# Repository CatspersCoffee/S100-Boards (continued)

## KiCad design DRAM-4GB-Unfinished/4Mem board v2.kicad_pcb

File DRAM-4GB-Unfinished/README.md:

# 4GB DRAM Board (4Mem v2): unfinished

A Spartan-6 XC6SLX45 + DDR3 DIMM mezzanine for the [x86 32bit Memory Adapter Board](../x86-Memory-Adapter/). It plugs onto the adapter's P8/P9 headers and isn't an S-100 card itself (2015).

## Status
**Unfinished: schematic and placed, partly routed PCB only. It was never routed or built.**
- The `GERBERS/` folder in the original project is empty.
- None of the 124 DDR3 nets or the 74 P8/P9 signal nets has a track. The PCB file reports 478 unrouted connections.
- The board has no title or revision text.

## Hardware
| Ref | Part | Role |
|---|---|---|
| U1 | XC6SLX45-2FGG484C | FPGA, DDR3 interface to the adapter board |
| U2 | 240-pin DDR3 DIMM socket | 64-bit unbuffered DIMM, 2 ranks |
| U3 | XCF08P (TSOP48) | FPGA configuration flash |
| U12 | PIC18F2520 (QFN28) | on the DIMM SPD I2C bus, 6 lines to the FPGA |
| U9 | oscillator | FPGA clock into ball M3 (GCLK); a 62.5 MHz 2.5 V part in `digikey.xlsx` |
| U5 | AZ1084 | 3.3 V from +8 V |
| U6 | NCP565 | 1.2 V (FPGA core) |
| U7 | LT1764EQ-1.5 | 1.5 V DIMM supply |
| U8 | RT9026 | DDR3 VTT / VREF |
| U4, U10 | LM1117-1.8, LM1117-2.5 | XCF08P core, oscillator |
| P8, P9 | 2x20 headers | to the x86 32bit Memory Adapter Board |
| P11 | 2x2 header | JTAG (TDI, TDO, TMS, TCK) |
| P5 | 2x6 header | PIC programming (MCLR/PGD/PGC) and UART (TX/RX) |
| SW1 | push button | FPGA PROG_B |
| D1, D2 | LEDs | POWER, FPGA DONE (via Q1) |

- Board: 150.4 x 75.2 mm, rounded corners, four corner mounting holes, 6 copper layers (Top, GND, Sig1, Sig2, POWER, Bottom).
- KiCad (2013-07-07 BZR 4022)-stable.

## How it works (as drawn)
- **P8/P9:** these carry 72 FPGA I/O lines plus +8 V (P8 pins 1–4) and GND (P9 pins 39–40). The pins and positions match P8/P9 on the [x86 32bit Memory Adapter Board](../x86-Memory-Adapter/): its 32-bit data bus (bD0–31), address bA2–22 and CPLD lines.
- **DDR3:** the FPGA connects to the whole DIMM interface: A0–A15, BA0–2, DQ0–63, DQS0–7, DM0–7, CK0/CK1, CKE0/1, S0/S1, ODT0/1, RAS/CAS/WE.
- **Configuration:** the FPGA boots from the XCF08P (D0–D7, CCLK), which shares the JTAG chain with the FPGA. SW1 pulls PROGRAM_B.
- **DIMM reset:** FPGA DONE drives the DIMM RESET# pin (through R8, 0 Ω) and the DONE LED.
- **PIC18F2520:** reads the DIMM SPD EEPROM (SCL/SDA, 10K pull-ups) and has 6 lines to the FPGA.
- **Power:** the board makes all its rails from the +8 V on P8.

## Files
| File | What it is |
|---|---|
| `4Mem board v2.sch` | schematic (single sheet) |
| `4Mem board v2-cache.lib` | symbol cache |
| `4Mem board v2.kicad_pcb` | PCB (placed, partly routed) |
| `4Mem board v2.pro` | KiCad project |
| `4Mem board v2.net`, `.cmp` | netlist and footprint assignments |
| `digikey.xlsx` | DigiKey parts list (NZD), including parts for the sibling SRAM/adapter boards |

There is no FPGA project for this board.

## History
- The git history replays the original dated backups, from 2015-05-03 to 2015-06-21.
- The project started as a copy of the [4Mbit (128K x 32) SRAM module](../x86-Memory-Adapter/sram-module/). It has the same outline and P8/P9 positions, and the module's "4Mbit (128K x 32)" text is still in the PCB file, outside the board edge.
- The last file activity is an autorouter (Specctra `.dsn`) export of the same PCB on 2016-12-06. It isn't included.

## Things to check (TODO)
- **FPGA supplies:** nets `/V1.2temp`, `/V1.5temp` and `/V3.3temp` are not joined to the regulator outputs `/V1.2`, `/V1.5` and `/V3.3`.
- **U4/U10 input:** `/+8Vitemp`, the input to U4 and U10, is not joined to `/+8Vi`.
- **XCF08P supply:** the XCF08P I/O supply is on a separate net, `/V3.3temp2`.
- **Loose pins:** one side of LEDs D5 and D6, and the PIC PGM pin, are unconnected.
- **DDR3 balls vs memory controller:** the DDR3 balls don't follow the Spartan-6 hard memory controller (MCB) pinout. For example, A0 is on G19, an M1A10 ball. The 64-bit DIMM is also wider than one MCB.
- **Net name:** `/DDR3_OFT1` is the DIMM ODT1 signal.
- **JTAG header:** P11 has no GND or VREF pin.
- **Schematic title block:** it still says "noname.sch".
- **Copper planes:** no copper zones are poured on the GND or POWER layers.

## Credits
- The DDR3 pin assignment follows a Spartan-6 DDR3 UDIMM reference document.
- The FPGA symbol comes from the author's own KiCad library.

## License
Hardware: CERN-OHL-S-2.0 for the original work in this folder; see the repo NOTICE for third-party parts.

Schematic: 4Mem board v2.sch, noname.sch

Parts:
C1, C4, C6, C14, C22, C23, C25, C26, C28, C29, C30, C31, C32, C33, C35, C37, C39, C40, C41, C42, C43, C45: 0.1 uF; C2
C2, C27: 0.1 uF
C3, C5, C7, C8, C9, C10, C11, C12, C13, C15, C16, C17, C18, C19, C20, C21, C24, C34, C36, C38, C44, C46, C47, C48: 10 uF
D1: POWER
D2: LED
D5, D6: LED; LEDV
P1, P2, P3, P4: CONN_1
P5: CONN_6X2
P8, P9: CONN_20X2; 8MB_SRAM
P11: CONN_2X2
Q1: ^^NPN-BC817-SOT323
R1, R2, R5, R6, R11: 330
R3, R4, R7, R9, R10: 4K7
R8: 0
R12, R13: 10K
SW1: PROG_B
U1: XC6SLX45-2FGG484C
U2: DDR3_DIMM_240PIN
U3: XCF08P-VO48/TSOP48
U4: LM1117MP-1.8
U5: AZ1084
U6: NCP565
U7: LT1764EQ-1.5
U8: RT9026_MSOP-10
U9: FPGA_CLK_0; Digikey CTX285LVCT-ND
U10: LM1117MP-2.5
U12: PIC18F2520-28QFN

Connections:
/+8Vi: C5.1, C7.1, C9.1, C10.1, C18.1, C34.1, P8.1, P8.2, P8.3, P8.4, U5.3 (VI), U6.1 (VI), U7.1 (~SHDN), U7.2 (VI)
/+8Vitemp: C3.1, C8.1, C44.1, U4.3 (VI), U10.3 (VI)
/DDR3_A0: U1.G19 (IO_L33P_A15_M1A10_1), U2.188 (A0)
/DDR3_A1: U1.A21 (IO_L20N_1), U2.181 (A1)
/DDR3_A2: U1.A20 (IO_L20P_1), U2.61 (A2)
/DDR3_A3: U1.A2 (IO_L83P_3), U2.180 (A3)
/DDR3_A4: U1.H8 (IO_L59N_3), U2.59 (A4)
/DDR3_A5: U1.G6 (IO_L55P_M3A13_3), U2.58 (A5)
/DDR3_A6: U1.F5 (IO_L55N_M3A14_3), U2.178 (A6)
/DDR3_A7: U1.G4 (IO_L51P_M3A10_3), U2.56 (A7)
/DDR3_A8: U1.H6 (IO_L49P_M3A7_3), U2.177 (A8)
/DDR3_A9: U1.J7 (IO_L59P_3), U2.175 (A9)
/DDR3_A10: U1.H19 (IO_L34P_A13_M1WE_1), U2.70 (A10/AP)
/DDR3_A11: U1.H5 (IO_L49N_M3A2_3), U2.55 (A11)
/DDR3_A12: U1.J6 (IO_L45N_M3ODT_3), U2.174 (A12/BC)
/DDR3_A13: U1.M20 (IO_L42P_GCLK7_M1UDM_1), U2.196 (A13)
/DDR3_A14: U1.K4 (IO_L43N_GCLK22_IRDY2_M3CASN_3), U2.172 (A14)
/DDR3_A15: U1.K3 (IO_L44P_GCLK21_M3A5_3), U2.171 (A15)
/DDR3_BA0: U1.J17 (IO_L36P_A9_M1BA0_1), U2.71 (BA0)
/DDR3_BA1: U1.H18 (IO_L34N_A12_M1BA2_1), U2.190 (BA1)
/DDR3_BA2: U1.J4 (IO_L44N_GCLK20_M3A6_3), U2.52 (BA2)
/DDR3_CAS: U1.K18 (IO_L61N_1), U2.74 (~CAS)
/DDR3_CK0h: U1.F18 (IO_L30P_A21_M1RESET_1), U2.184 (CK0)
/DDR3_CK0l: U1.F19 (IO_L30N_A20_M1A11_1), U2.185 (~CK0)
/DDR3_CK1h: U1.B21 (IO_L19P_1), U2.63 (CK1)
/DDR3_CK1l: U1.B22 (IO_L19N_1), U2.64 (~CK1)
/DDR3_CKE0: U1.K5 (IO_L43P_GCLK23_M3RASN_3), U2.50 (CKE0)
/DDR3_CKE1: U1.K6 (IO_L45P_M3A3_3), U2.169 (CKE1)
/DDR3_DM0: U1.V1 (IO_L32N_M3DQ15_3), U2.125 (DM0)
/DDR3_DM1: U1.P1 (IO_L36N_M3DQ9_3), U2.134 (DM1)
/DDR3_DM2: U1.J1 (IO_L41N_GCLK26_M3DQ5_3), U2.143 (DM2)
/DDR3_DM3: U1.E3 (IO_L52P_M3A8_3), U2.152 (DM3)
/DDR3_DM4: U1.D22 (IO_L31N_A18_M1A12_1), U2.203 (DM4)
/DDR3_DM5: U1.H22 (IO_L41N_GCLK8_M1CASN_1), U2.212 (DM5)
/DDR3_DM6: U1.M19 (IO_L53P_1), U2.221 (DM6)
/DDR3_DM7: U1.U22 (IO_L51N_M1DQ13_1), U2.230 (DM7)
/DDR3_DQ0: U1.W3 (IO_L2P_3), U2.3 (DQ0)
/DDR3_DQ1: U1.W1 (IO_L2N_3), U2.4 (DQ1)
/DDR3_DQ2: U1.U3 (IO_L33P_M3DQ12_3), U2.9 (DQ2)
/DDR3_DQ3: U1.T1 (IO_L34N_M3UDQSN_3), U2.10 (DQ3)
/DDR3_DQ4: U1.Y2 (IO_L1P_3), U2.122 (DQ4)
/DDR3_DQ5: U1.V2 (IO_L32P_M3DQ14_3), U2.123 (DQ5)
/DDR3_DQ6: U1.U1 (IO_L33N_M3DQ13_3), U2.128 (DQ6)
/DDR3_DQ7: U1.T2 (IO_L34P_M3UDQS_3), U2.129 (DQ7)
/DDR3_DQ8: U1.T4 (IO_L9P_3), U2.12 (DQ8)
/DDR3_DQ9: U1.R3 (IO_L35P_M3DQ10_3), U2.13 (DQ9)
/DDR3_DQ10: U1.M1 (IO_L38N_M3DQ3_3), U2.18 (DQ10)
/DDR3_DQ11: U1.L1 (IO_L39N_M3LDQSN_3), U2.19 (DQ11)
/DDR3_DQ12: U1.T3 (IO_L9N_3), U2.131 (DQ12)
/DDR3_DQ13: U1.R1 (IO_L35N_M3DQ11_3), U2.132 (DQ13)
/DDR3_DQ14: U1.M2 (IO_L38P_M3DQ2_3), U2.137 (DQ14)
/DDR3_DQ15: U1.L3 (IO_L39P_M3LDQS_3), U2.138 (DQ15)
/DDR3_DQ16: U1.K1 (IO_L40N_M3DQ7_3), U2.21 (DQ16)
/DDR3_DQ17: U1.K2 (IO_L40P_M3DQ6_3), U2.22 (DQ17)
/DDR3_DQ18: U1.H2 (IO_L47P_M3A0_3), U2.27 (DQ18)
/DDR3_DQ19: U1.G1 (IO_L48N_M3BA1_3), U2.28 (DQ19)
/DDR3_DQ20: U1.M5 (IO_L31P_3), U2.140 (DQ20)
/DDR3_DQ21: U1.J3 (IO_L41P_GCLK27_M3DQ4_3), U2.141 (DQ21)
/DDR3_DQ22: U1.H1 (IO_L47N_M3A1_3), U2.146 (DQ22)
/DDR3_DQ23: U1.G3 (IO_L48P_M3BA0_3), U2.147 (DQ23)
/DDR3_DQ24: U1.F1 (IO_L50N_M3BA2_3), U2.30 (DQ24)
/DDR3_DQ25: U1.E1 (IO_L52N_M3A9_3), U2.31 (DQ25)
/DDR3_DQ26: U1.C3 (IO_L54P_M3RESET_3), U2.36 (DQ26)
/DDR3_DQ27: U1.B2 (IO_L60P_3), U2.37 (DQ27)
/DDR3_DQ28: U1.F3 (IO_L51N_M3A4_3), U2.149 (DQ28)
/DDR3_DQ29: U1.F2 (IO_L50P_M3WE_3), U2.150 (DQ29)
/DDR3_DQ30: U1.C1 (IO_L54N_M3A11_3), U2.155 (DQ30)
/DDR3_DQ31: U1.B1 (IO_L60N_3), U2.156 (DQ31)
/DDR3_DQ32: U1.C22 (IO_L32N_A16_M1A9_1), U2.81 (DQ32)
/DDR3_DQ33: U1.C20 (IO_L32P_A17_M1A8_1), U2.82 (DQ33)
/DDR3_DQ34: U1.E20 (IO_L35P_A11_M1A7_1), U2.87 (DQ34)
/DDR3_DQ35: U1.F22 (IO_L37N_A6_M1A1_1), U2.88 (DQ35)
/DDR3_DQ36: U1.C19 (IO_L1P_A25_1), U2.200 (DQ36)
/DDR3_DQ37: U1.D21 (IO_L31P_A19_M1CKE_1), U2.201 (DQ37)
/DDR3_DQ38: U1.E22 (IO_L35N_A10_M1A2_1), U2.206 (DQ38)
/DDR3_DQ39: U1.F21 (IO_L37P_A7_M1A0_1), U2.207 (DQ39)
/DDR3_DQ40: U1.G22 (IO_L39N_M1ODT_1), U2.90 (DQ40)
/DDR3_DQ41: U1.H21 (IO_L41P_GCLK9_IRDY1_M1RASN_1), U2.91 (DQ41)
/DDR3_DQ42: U1.J20 (IO_L43P_GCLK5_M1DQ4_1), U2.96 (DQ42)
/DDR3_DQ43: U1.K21 (IO_L44P_A3_M1DQ6_1), U2.97 (DQ43)
/DDR3_DQ44: U1.F20 (IO_L33N_A14_M1A4_1), U2.209 (DQ44)
/DDR3_DQ45: U1.G20 (IO_L39P_M1A3_1), U2.210 (DQ45)
/DDR3_DQ46: U1.J22 (IO_L43N_GCLK4_M1DQ5_1), U2.215 (DQ46)
/DDR3_DQ47: U1.K22 (IO_L44N_A2_M1DQ7_1), U2.216 (DQ47)
/DDR3_DQ48: U1.L20 (IO_L45P_A1_M1LDQS_1), U2.99 (DQ48)
/DDR3_DQ49: U1.M21 (IO_L46P_FCS_B_M1DQ2_1), U2.100 (DQ49)
/DDR3_DQ50: U1.P21 (IO_L48P_HDC_M1DQ8_1), U2.105 (DQ50)
/DDR3_DQ51: U1.R22 (IO_L49N_M1DQ11_1), U2.106 (DQ51)
/DDR3_DQ52: U1.L22 (IO_L45N_A0_M1LDQSN_1), U2.218 (DQ52)
/DDR3_DQ53: U1.M22 (IO_L46N_FOE_B_M1DQ3_1), U2.219 (DQ53)
/DDR3_DQ54: U1.P22 (IO_L48N_M1DQ9_1), U2.224 (DQ54)
/DDR3_DQ55: U1.R20 (IO_L49P_M1DQ10_1), U2.225 (DQ55)
/DDR3_DQ56: U1.T22 (IO_L50N_M1UDQSN_1), U2.108 (DQ56)
/DDR3_DQ57: U1.U20 (IO_L51P_M1DQ12_1), U2.109 (DQ57)
/DDR3_DQ58: U1.V21 (IO_L52P_M1DQ14_1), U2.114 (DQ58)
/DDR3_DQ59: U1.W22 (IO_L60N_1), U2.115 (DQ59)
/DDR3_DQ60: U1.P19 (IO_L59P_1), U2.227 (DQ60)
/DDR3_DQ61: U1.T21 (IO_L50P_M1UDQS_1), U2.228 (DQ61)
/DDR3_DQ62: U1.V22 (IO_L52N_M1DQ15_1), U2.233 (DQ62)
/DDR3_DQ63: U1.W20 (IO_L60P_1), U2.234 (DQ63)
/DDR3_DQS0h: U1.U4 (IO_L10P_3), U2.7 (DQS0)
/DDR3_DQS0l: U1.V3 (IO_L10N_3), U2.6 (~DQS0)
/DDR3_DQS1h: U1.N1 (IO_L37N_M3DQ1_3), U2.16 (DQS1)
/DDR3_DQS1l: U1.N3 (IO_L37P_M3DQ0_3), U2.15 (~DSQ1)
/DDR3_DQS2h: U1.H3 (IO_L46N_M3CLKN_3), U2.25 (DQS2)
/DDR3_DQS2l: U1.H4 (IO_L46P_M3CLK_3), U2.24 (~DQS2)
/DDR3_DQS3h: U1.D2 (IO_L53P_M3CKE_3), U2.34 (DQS3)
/DDR3_DQS3l: U1.D1 (IO_L53N_M3A12_3), U2.33 (~DQS3)
/DDR3_DQS4h: U1.D19 (IO_L29P_A23_M1A13_1), U2.85 (DQS4)
/DDR3_DQS4l: U1.D20 (IO_L29N_A22_M1A14_1), U2.84 (~DQS4)
/DDR3_DQS5h: U1.J19 (IO_L38N_A4_M1CLKN_1), U2.94 (DQS5)
/DDR3_DQS5l: U1.H20 (IO_L38P_A5_M1CLK_1), U2.93 (~DQS5)
/DDR3_DQS6h: U1.N20 (IO_L47P_FWE_B_M1DQ0_1), U2.103 (DQS6)
/DDR3_DQS6l: U1.N22 (IO_L47N_LDC_M1DQ1_1), U2.102 (~DQS6)
/DDR3_DQS7h: U1.T19 (IO_L74P_AWAKE_1), U2.112 (DQS7)
/DDR3_DQS7l: U1.T20 (IO_L74N_DOUT_BUSY_1), U2.111 (~DQS7)
/DDR3_ODT0: U1.L19 (IO_L42N_GCLK6_TRDY1_M1LDM_1), U2.195 (~DQS0)
/DDR3_OFT1: U1.P20 (IO_L59N_1), U2.77 (OFT1)
/DDR3_RAS: U1.K17 (IO_L36N_A8_M1BA1_1), U2.192 (~RAS)
/DDR3_S0l: U1.K19 (IO_L40N_GCLK10_M1A6_1), U2.193 (~SO)
/DDR3_S1l: U1.L17 (IO_L61P_1), U2.76 (~S1)
/DDR3_SCL: R12.1, U2.118 (SCL), U12.11 (SCK/SCL/RC3)
/DDR3_SDA: R13.1, U2.238 (SDA), U12.12 (SDI/SDA/RC4)
/DDR3_VREF: C23.1, C26.1, C29.1, C31.1, U2.1 (VREF), U2.67 (VREF), U8.6 (VTTREF)
/DDR3_VTT: C22.1, C25.1, C28.1, C30.1, U2.120 (VTT), U2.240 (VTT), U8.3 (VTT), U8.5 (VTTSNS)
/DDR3_WE: U1.K20 (IO_L40P_GCLK11_M1A5_1), U2.73 (~WE)
/DONE_LED_SIGNAL: Q1.1 (B), R8.1, U2.168 (~RESET)
/FPGA_CCLK_2: R3.2, R4.1, U1.Y21 (IO_L1P_CCLK_2), U3.12 (CLK)
/FPGA_CLK_0: U1.M3 (IO_L42P_GCLK25_TRDY2_M3UDM_3), U9.3 (OUT)
/FPGA_DONE: R8.2, R11.2, U1.Y22 (DONE_2), U3.13 (CE)
/FPGA_INIT_B: R7.2, U1.T6 (IO_L65P_INIT_B_2), U3.11 (OE/RST)
/FPGA_PROGRAM_B: R10.2, SW1.2, U1.AA1 (PROGRAM_B_2)
/FPGA_TDI: P11.3, U1.E18 (TDI)
/FPGA_TDO: U1.A19 (TDO), U3.19 (TDI)
/IO_000: P8.13, U1.B14 (IO_L50P_0)
/IO_001: P8.15, U1.A14 (IO_L50N_0)
/IO_002: P8.17, U1.A17 (IO_L64N_SCP4_0)
/IO_003: P8.19, U1.B18 (IO_L65P_SCP3_0)
/IO_004: P8.21, U1.A16 (IO_L63N_SCP6_0)
/IO_005: P8.23, U1.C17 (IO_L64P_SCP5_0)
/IO_006: P8.25, U1.C16 (IO_L62N_VREF_0)
/IO_007: P8.27, U1.B16 (IO_L63P_SCP7_0)
/IO_008: P8.29, U1.B6 (IO_L4P_0)
/IO_009: P8.31, U1.A6 (IO_L4N_0)
/IO_010: P8.33, U1.C7 (IO_L5P_0)
/IO_011: P8.35, U1.A7 (IO_L5N_0)
/IO_012: P8.37, U1.B8 (IO_L6P_0)
/IO_013: P8.39, U1.A8 (IO_L6N_0)
/IO_014: P9.1, U1.B10 (IO_L34P_GCLK19_0)
/IO_015: P9.3, U1.A10 (IO_L34N_GCLK18_0)
/IO_016: P9.5, U1.AB9 (IO_L43N_2)
/IO_017: P9.7, U1.Y9 (IO_L43P_2)
/IO_018: P9.9, U1.Y10 (IO_L44N_2)
/IO_019: P9.11, U1.W10 (IO_L44P_2)
/IO_020: P9.13, U1.Y16 (IO_L17P_2)
/IO_021: P9.15, U1.W15 (IO_L17N_2)
/IO_022: P9.17, U1.B12 (IO_L37P_GCLK13_0)
/IO_023: P9.19, U1.A12 (IO_L37N_GCLK12_0)
/IO_024: P9.21, U1.C13 (IO_L38P_0)
/IO_025: P9.23, U1.A13 (IO_L38N_VREF_0)
/IO_026: P9.25, U1.D14 (IO_L49P_0)
/IO_027: P9.27, U1.C14 (IO_L49N_0)
/IO_028: P9.29, U1.U16 (IO_L8N_2)
/IO_029: P9.31, U1.U17 (IO_L8P_2)
/IO_030: P9.33, U1.W8 (IO_L46P_2)
/IO_031: P9.35, U1.Y8 (IO_L47N_2)
/IO_032: P9.37, U1.C6 (IO_L3N_0)
/IO_033: P9.34, U1.D6 (IO_L3P_0)
/IO_034: P9.36, U1.A5 (IO_L2N_0)
/IO_035: P9.38, U1.C5 (IO_L2P_0)
/IO_072: P8.5, U1.AA18 (IO_L14P_D11_2)
/IO_073: P8.7, U1.AB18 (IO_L14N_D12_2)
/IO_074: P8.9, U1.U10 (IO_L52N_2)
/IO_075: P8.11, U1.T10 (IO_L52P_2)
/IO_076: P9.18, U1.W14 (IO_L20P_2)
/IO_077: P9.20, U1.Y14 (IO_L20N_2)
/IO_078: P9.22, U1.Y15 (IO_L21P_2)
/IO_079: P9.24, U1.AB15 (IO_L21N_2)
/IO_080: P9.26, U1.AB12 (IO_L31N_GCLK30_D15_2)
/IO_081: P9.28, U1.AA12 (IO_L31P_GCLK31_D14_2)
/IO_082: P9.30, U1.AB11 (IO_L32N_GCLK28_2)
/IO_083: P9.32, U1.Y11 (IO_L32P_GCLK29_2)
/IO_084: P9.6, U1.AB5 (IO_L54N_2)
/IO_085: P9.8, U1.Y5 (IO_L54P_2)
/IO_086: P9.10, U1.AB3 (IO_L58N_2)
/IO_087: P9.12, U1.Y3 (IO_L58P_2)
/IO_088: P9.14, U1.Y6 (IO_L53N_2)
/IO_089: P9.16, U1.W6 (IO_L53P_2)
/IO_090: P8.38, U1.AB10 (IO_L41N_VREF_2)
/IO_091: P8.40, U1.AA10 (IO_L41P_2)
/IO_092: P9.2, U1.AB4 (IO_L57N_2)
/IO_093: P9.4, U1.AA4 (IO_L57P_2)
/IO_094: P8.6, U1.W12 (IO_L29P_GCLK3_2)
/IO_095: P8.8, U1.Y12 (IO_L29N_GCLK2_2)
/IO_096: P8.10, U1.AA16 (IO_L19P_2)
/IO_097: P8.12, U1.AB16 (IO_L19N_2)
/IO_098: P8.14, U1.AA14 (IO_L16P_2)
/IO_099: P8.16, U1.AB14 (IO_L16N_VREF_2)
/IO_100: P8.18, U1.Y19 (IO_L5P_2)
/IO_101: P8.20, U1.AB19 (IO_L5N_2)
/IO_102: P8.22, U1.Y17 (IO_L15P_2)
/IO_103: P8.24, U1.AB17 (IO_L15N_2)
/IO_104: P8.26, U1.W18 (IO_L6P_2)
/IO_105: P8.28, U1.Y18 (IO_L6N_2)
/IO_106: P8.30, U1.U6 (IO_L63P_2)
/IO_107: P8.32, U1.V5 (IO_L63N_2)
/IO_108: P8.34, U1.AB8 (IO_L45N_2)
/IO_109: P8.36, U1.AA8 (IO_L45P_2)
/PF_D0: U1.AA20 (IO_L3P_D0_DIN_MISO_MISO1_2), U3.28 (D0)
/PF_D1: U1.U14 (IO_L12P_D1_MISO2_2), U3.29 (D1)
/PF_D2: U1.U13 (IO_L12N_D2_MISO3_2), U3.32 (D2)
/PF_D3: U1.AA6 (IO_L49P_D3_2), U3.33 (D3)
/PF_D4: U1.AB6 (IO_L49N_D4_2), U3.43 (D4)
/PF_D5: U1.W4 (IO_L62P_D5_2), U3.44 (D5)
/PF_D6: U1.Y4 (IO_L62N_D6_2), U3.47 (D6)
/PF_D7: U1.Y7 (IO_L48P_D7_2), U3.48 (D7)
/PF_TDO: P11.1, U3.22 (TDO)
/PIC_IO1: U1.W11 (IO_L42N_2), U12.18 (INT0/FLT0/AN12/RB0)
/PIC_IO2: U1.V11 (IO_L42P_2), U12.19 (INT1/AN10/RB1)
/PIC_IO3: U1.V19 (IO_L9P_2), U12.20 (INT2/AN8/RB2)
/PIC_IO4: U1.V18 (IO_L9N_2), U12.21 (CCP2/AN9/RB3)
/PIC_IO5: U1.R16 (IO_L10P_2), U12.8 (T1OSO/T13CKI/RC0)
/PIC_IO6: U1.R15 (IO_L10N_2), U12.9 (CCP2/T1OSI/CCP2/RC1)
/PIC_MCLR: P5.1, U12.26 (_MCLR/VPP/RE3)
/PIC_PGC: P5.9, U12.24 (KBI2/PGC/RB6)
/PIC_PGD: P5.7, U12.25 (KBI3/PGD/RB7)
/PIC_RX: P5.4, P5.10, U12.15 (RX/DT/RC7)
/V1.2: C12.1, C16.1, C20.1, U6.3 (VO)
/V1.2temp: C2.1, C33.1, C37.1, C40.1, C41.1, C43.1, U1.J8 (VCCINT), U1.J10 (VCCINT), U1.J12 (VCCINT), U1.J14 (VCCINT), U1.K9 (VCCINT), U1.K11 (VCCINT), U1.K13 (VCCINT), U1.L10 (VCCINT), U1.L12 (VCCINT), U1.L14 (VCCINT), U1.M9 (VCCINT), U1.M11 (VCCINT), U1.M13 (VCCINT), U1.N10 (VCCINT), U1.N12 (VCCINT), U1.N14 (VCCINT), U1.P9 (VCCINT), U1.P11 (VCCINT), U1.P13 (VCCINT), U1.R14 (VCCINT)
/V1.5: C13.1, C17.1, C21.1, U2.51 (VCC), U2.54 (VCC), U2.57 (VCC), U2.60 (VCC), U2.62 (VCC), U2.65 (VCC), U2.66 (VCC), U2.69 (VCC), U2.72 (VCC), U2.75 (VCC), U2.78 (VCC), U2.170 (VCC), U2.173 (VCC), U2.176 (VCC), U2.179 (VCC), U2.182 (VCC), U2.183 (VCC), U2.186 (VCC), U2.189 (VCC), U2.191 (VCC), U2.194 (VCC), U2.197 (VCC), U7.4 (VO), U7.5 (SENSE/ADJ), U8.1 (VDDQSNS), U8.2 (VLDOIN)
/V1.5temp: U1.C2 (VCCO_3), U1.C21 (VCCO_1), U1.E19 (VCCO_1), U1.F4 (VCCO_3), U1.F6 (VCCO_3), U1.G2 (VCCO_3), U1.G21 (VCCO_1), U1.J5 (VCCO_3), U1.J18 (VCCO_1), U1.L2 (VCCO_3), U1.L7 (VCCO_3), U1.L16 (VCCO_1), U1.L21 (VCCO_1), U1.N5 (VCCO_3), U1.N18 (VCCO_1), U1.R2 (VCCO_3), U1.R21 (VCCO_1), U1.U5 (VCCO_3), U1.U18 (VCCO_1), U1.W2 (VCCO_3), U1.W21 (VCCO_1)
/V1.8: C11.1, C15.1, C19.1, U3.4 (VCCINT), U3.15 (VCCINT), U3.34 (VCCINT), U4.2 (VO)
/V2.5: C46.1, C47.1, C48.1, U9.1 (OE/StandBy), U9.4 (VDD), U10.2 (VO)
/V3.3temp: C1.1, C4.1, C6.1, C14.1, C27.1, C32.1, C35.1, C39.1, C42.1, R2.1, R10.1, R11.1, U1.AA3 (VCCO_2), U1.AA7 (VCCO_2), U1.AA11 (VCCO_2), U1.AA15 (VCCO_2), U1.AA19 (VCCO_2), U1.B4 (VCCO_0), U1.B7 (VCCO_0), U1.B11 (VCCO_0), U1.B15 (VCCO_0), U1.B19 (VCCO_0), U1.D16 (VCCAUX), U1.E9 (VCCO_0), U1.E13 (VCCO_0), U1.E17 (VCCO_0), U1.F11 (VCCAUX), U1.G10 (VCCO_0), U1.G12 (VCCAUX), U1.G14 (VCCO_0), U1.H9 (VCCAUX), U1.H15 (VCCAUX), U1.K15 (VCCAUX), U1.L8 (VCCAUX), U1.M15 (VCCAUX), U1.N8 (VCCAUX), U1.R6 (VCCAUX), U1.R10 (VCCAUX), U1.R12 (VCCAUX), U1.T9 (VCCO_2), U1.T13 (VCCO_2), U1.U11 (VCCAUX), U1.V6 (VCCAUX), U1.V8 (VCCO_2), U1.V12 (VCCO_2), U1.V16 (VCCO_2), U1.W5 (VCCO_2)
/V3.3temp2: R3.1, R7.1, R9.1, U3.8 (VCCO), U3.24 (VCCJ), U3.30 (VCCO), U3.38 (VCCO), U3.45 (VCCO)
/mm_TCK: P11.4, U1.G15 (TCK), U3.20 (TCK)
/mm_TMS: P11.2, U1.C18 (TMS), U3.21 (TMS)
GND: C1.2, C2.2, C3.2, C4.2, C5.2, C6.2, C7.2, C8.2, C9.2, C10.2, C11.2, C12.2, C13.2, C14.2, C15.2, C16.2, C17.2, C18.2, C19.2, C20.2, C21.2, C22.2, C23.2, C24.2, C25.2, C26.2, C27.2, C28.2, C29.2, C30.2, C31.2, C32.2, C33.2, C34.2, C35.2, C36.2, C37.2, C38.2, C39.2, C40.2, C41.2, C42.2, C43.2, C44.2, C45.2, C46.2, C47.2, C48.2, D1.2 (K), P1.1, P2.1, P3.1, P4.1, P5.2, P5.5, P5.12, P9.39, P9.40, Q1.2 (E), R4.2, R5.1, R6.1, SW1.1, U1.A1 (GND), U1.A3 (IO_L1P_HSWAPEN_0), U1.A22 (GND), U1.AA5 (GND), U1.AA9 (GND), U1.AA13 (GND), U1.AA17 (GND), U1.AA22 (IO_L1N_M0_CMPMISO_2), U1.AB1 (GND), U1.AB7 (IO_L48N_RDWR_B_VREF_2), U1.AB20 (IO_L3N_MOSI_CSI_B_MISO0_2), U1.AB22 (GND), U1.B5 (GND), U1.B9 (GND), U1.B13 (GND), U1.B17 (GND), U1.D4 (GND)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
unnamed: D2.2 (K), Q1.3 (C)
unnamed: D2.1 (A), R2.2
unnamed: R9.2, U3.6 (CF)
unnamed: D6.2 (K), R5.2
unnamed: D5.2 (K), R6.2
unnamed: D1.1 (A), R1.2

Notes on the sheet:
CPLD XC9532XL VQ44
POWER
3.3V Fixed 5A, 6.3 V- 12 V TO-232-3 Digi# AZ1084CS2-3.3TRE1DICT-ND
MOUNTING HOLES
LOGOs
Unused CPLD pins
LED's
Signals coming from CPLD for these
I/O from connector to/from CPLD
D11 C12 A3 A4 D7 D8 B8 A8 D6 C6 C5 A5 B6 A6 C7 A7
XCF16P - VOG48
FPGA pin D0 -> AA20 D1 -> U14 D2 -> U13 D3 -> AA6 D4 -> AB6 D5 -> W4 D6 -> Y4 D7 -> Y7 M0 -> AA22 M1 -> U15 HSWAPEN -> A3 DONE_2 -> Y22 CCLK -> Y21 INIT_B -> T6 CSI_B -> AB20 CSO_B -> T5 PROGRAM_B -> AA1 RDWR_B -> AB7 DOUT_BUSY -> T20 SUSPEND -> N15 TCK -> G15 TDI -> E18 TMS -> C18 TDO -> A19
output from PF -> into Adapter board from Adapter board -> input to FPGA
W12 Y12 AA14 AB14 AA21 AB21 Y19 AB19 U15 V15 Y21 AA22 T6 T5 AA20 AB20
1.2V
1.2V Fixed 1.5A , Vin 2.5 V-9 V TO-232-3 Digi# NCP565D2T12GOS-ND
3.3V
2+tab
1.5V
1.5V Fixed 3A , Vin 2.7 V- 20 V TO-263-6, D²Pak (5 Leads + Tab), TO-263BA LT1764EQ-1.5#PBF-ND
1.8V Fixed 800mA, up to 15 V SOT-223 Digi# LM1117MP-1.8/NOPBCT-ND
1.8V
from Adapter board -> input to FPGA
output from PF -> into Adapter board
JTAG Chain
DONE_LED
PROG_B
Leave unconnected or pull to VCCO_2
2.5V Fixed 1.5A, up to 15 Vin SOT-223 Digi# LM1117MPX-2.5/NOPBCT-ND or ebay: AMS1117-2.5
2.5V
FPGA DONE Signal: Active-High signal indicating configuration is complete: 0 = FPGA not configured 1 = FPGA configured

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
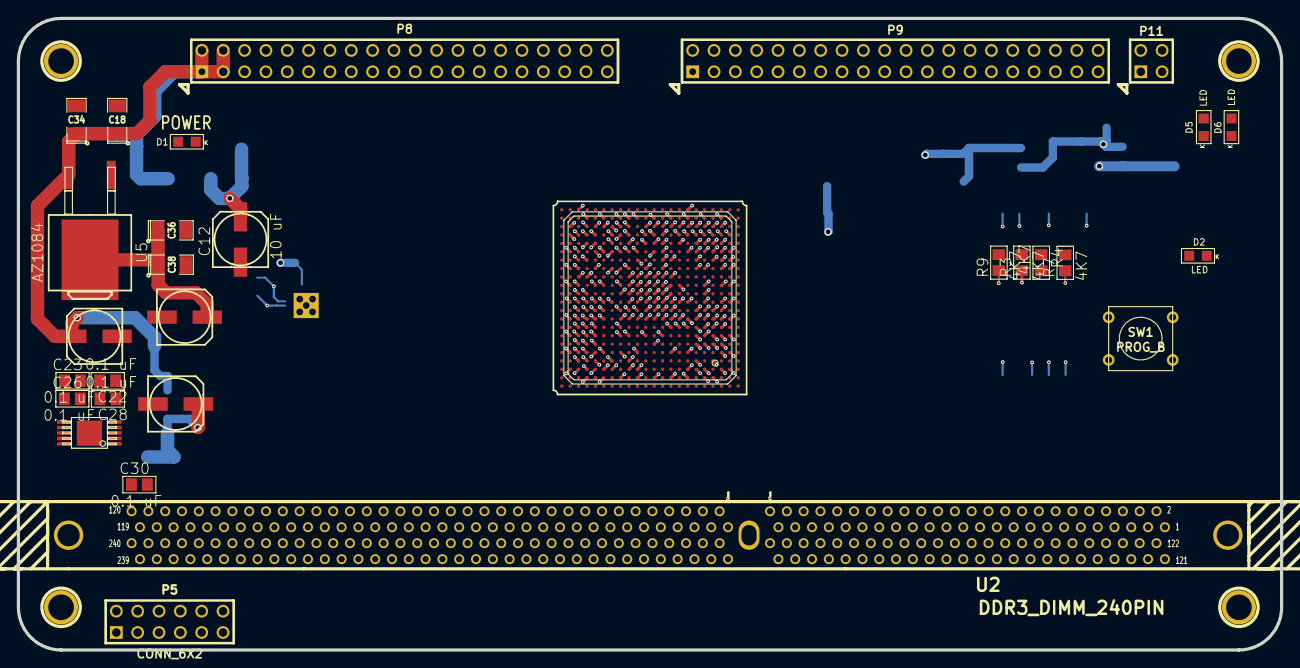
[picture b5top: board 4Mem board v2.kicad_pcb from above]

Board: 6 copper layers, 150.4 x 75.2 mm, 86 parts (0 on the bottom side), 246 nets.

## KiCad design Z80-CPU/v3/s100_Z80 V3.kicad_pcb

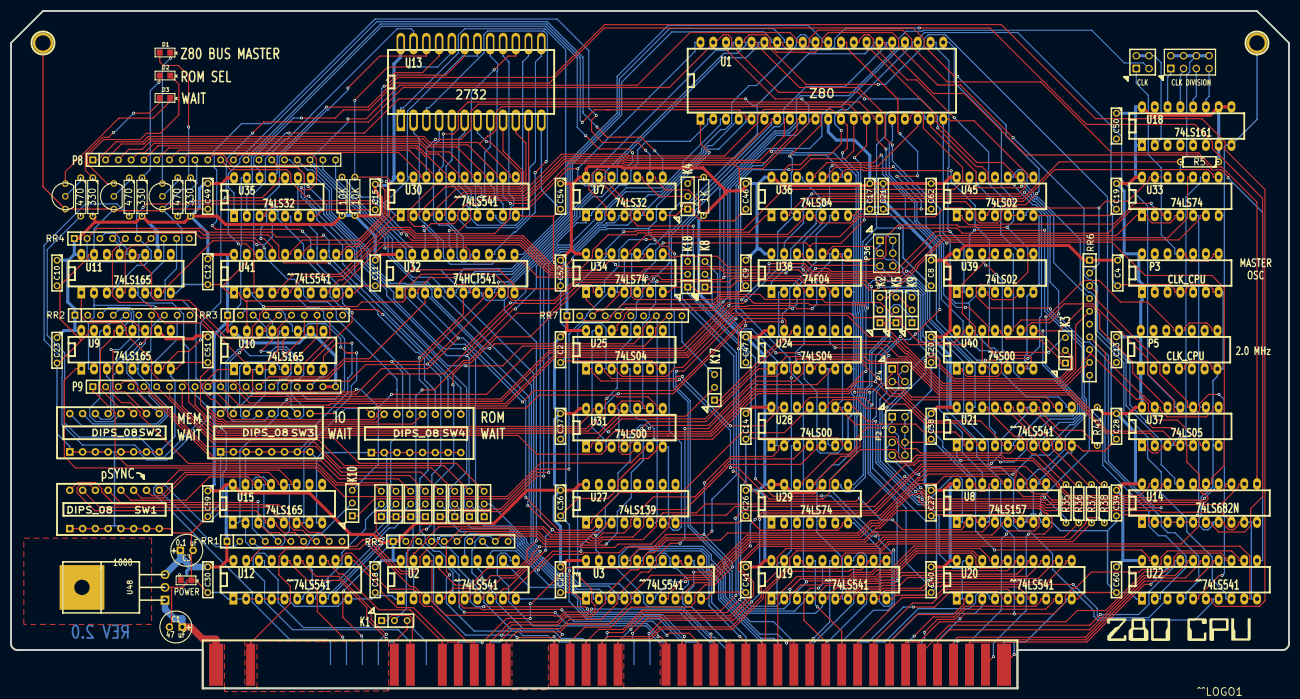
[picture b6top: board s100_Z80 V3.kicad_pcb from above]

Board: 2 copper layers, 254.0 x 134.6 mm, 140 parts (0 on the bottom side), 291 nets.

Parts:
C1: 47 uF; C1V7
C2, C4, C8, C9, C10, C11, C12, C13, C14, C15, C17, C18, C19, C20, C23, C25, C26, C27, C28, C30, C36, C37, C38, C39, C40, C41, C46, C47, C49, C50, C51, C52, C54, C59, C60, C62: 0.1 uF; C2
C3: 0.1 uF; C1V7
C21: 100nF; C2
D1, D2: DONE; ^^LED-0805
D3: WAIT; ^^LED-0805
D8: D2-1; ^^LED-0805
K1, K2, K4: CONN_3; SIL-3
K3: pSYNCdata; SIL-3
K5: pSYNC; SIL-3
K6: bA15; SIL-3
K7: bA14; SIL-3
K8: WRstrobe; SIL-3
K9: U29B Q; SIL-3
K10: U15 Clock; SIL-3
K11: bA13; SIL-3
K12: bA12; SIL-3
K13: bA19; SIL-3
K14: bA18; SIL-3
K15: bA16; SIL-3
K16: bA17; SIL-3
K17: EN_WAITS; SIL-3
K18: ROM_E-; SIL-3
P1: S100_MALE
P2: CONN_4X2; pin_array_4x2
P3, P5: CLK_CPU; DIP-14__300_ELL
P4: CONN_2X2; PIN_ARRAY_2X2
P6: MASTER_OSC; PIN_ARRAY_2X2
P7: CLK_SEL; Pin_Array_4X2
P8, P9: CONN_20; ^^SIL-20
P34, P35: CONN_1; 1pin
P36: CONN_3X2; pin_array_3x2
Q1, Q2, Q3: NPN; ^^TO92-inline
R1, R3, R5, R8: 330; R3
R2, R6, R9: 470; R3
R4: 330; ^^SMD_Resistor-0805
R7: 1K; R3
R11, R16: 10K; R3
R35, R36, R37, R38: 10; R3
R41: 4700; R3
RR1, RR2, RR3, RR4, RR5, RR6: 1000; r_pack9
RR7: 4700; r_pack9
SW1, SW2, SW3, SW4: DIPS_08; SWDIP8
U1: Z80; DIP-40__600_ELL
U2, U3, U12, U19, U20, U21, U22, U30, U41: ^^74LS541; DIP-20__300_ELL
U7, U35: 74LS32; DIP-14__300_ELL
U8: 74LS157; DIP-16__300_ELL
U9, U10, U11, U15: 74LS165; DIP-16__300_ELL
U13: 2732; ^^DIP-24-ZIF
U14: 74LS682N; DIP-20__300_ELL
U18: 74LS161; DIP-16__300_ELL
U24, U25, U36: 74LS04; DIP-14__300_ELL
U26: ^^LOGO1; ***Z80cpuV32
U27: 74LS139; DIP-16__300_ELL
U28, U31: 74LS00; DIP-14__300_ELL
U29, U33, U34: 74LS74; DIP-14__300_ELL
U32: 74HCT541; DIP-20__300_ELL
U37: 74LS05; DIP-14__300_ELL
U38: 74F04; DIP-14__300_ELL
U39, U45: 74LS02; DIP-14__300_ELL
U40: 74S00; DIP-14__300_ELL
U48: LDO_REG_7805; ^^TO220

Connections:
/2MHZ_CLOCK: P5.8, P5.11, U21.7
/27_ROM_OE: U28.10, U36.5, U40.8, U41.8
/+8V: C1.1, P1.1, P1.51, U48.1
/A0: P1.79, U2.11
/A1: P1.80, U2.12
/A2: P1.81, U2.13
/A3: P1.31, U2.14
/A4: P1.30, U2.15
/A5: P1.29, U2.16
/A6: P1.82, U2.17
/A7: P1.83, U2.18
/A8: P1.84, U3.11
/A9: P1.34, U3.12
/A10: P1.37, U3.13
/A11: P1.87, U3.14
/A12: P1.33, U3.15
/A13: P1.85, U3.16
/A14: P1.86, U3.17
/A15: P1.32, U3.18
/A16: P1.16, U12.11
/A17: P1.17, U12.12
/A18: P1.15, U12.13
/A19: P1.59, U12.14
/A20: P1.61, U12.15
/A21: P1.62, U12.16
/A22: P1.63, U12.17
/A23: P1.64, U12.18
/ADSB: U2.19, U3.19, U12.19, U24.2
/ADSB*: P1.22, RR5.9, U24.1, U37.4
/BUSAK*: U1.23, U36.13, U37.11
/BUSRQ*: U1.25, U34.5
/CDSB*: P1.19, RR6.7, U37.8, U37.13
/CLK_CPU: K10.3, P7.2, P7.4, P7.6, P7.8, R5.2, U1.6, U9.2, U10.2, U11.2, U33.11, U36.3
/CLOCK*: P1.49, P4.2
/D0: P8.8, U1.14, U19.9, U20.11, U30.18
/D1: P8.7, U1.15, U19.8, U20.12, U30.17
/D2: P8.6, U1.12, U19.7, U20.13, U30.16
/D3: P8.5, U1.8, U19.6, U20.14, U30.15
/D4: P8.4, U1.7, U19.5, U20.15, U30.14
/D5: P8.3, U1.9, U19.4, U20.16, U30.13
/D6: P8.2, U1.10, U19.3, U20.17, U30.12
/D7: P8.1, U1.13, U19.2, U20.18, U30.11
/DATA_OUT_ENABLE: K8.3, U20.1, U20.19, U28.8
/DI0: P1.95, U20.9
/DI1: P1.94, U20.8
/DI2: P1.41, U20.7
/DI3: P1.42, U20.6
/DI4: P1.91, U20.5
/DI5: P1.92, U20.4
/DI6: P1.93, U20.3
/DI7: P1.43, U20.2
/DO0: P1.36, U19.11
/DO1: P1.35, U19.12
/DO2: P1.88, U19.13
/DO3: P1.89, U19.14
/DO4: P1.38, U19.15
/DO5: P1.39, U19.16
/DO6: P1.40, U19.17
/DO7: P1.90, U19.18
/DODSB*: P1.23, RR5.8, U28.2, U37.2
/ERROR*: P1.98, RR6.10
/HALT*: U1.18, U38.1
/HOLD*: P1.74, RR5.4, U34.2, U45.2
/INT*: P1.73, RR5.3, U21.9
/IORQ*: P9.10, U1.20, U38.5, U39.3, U39.6, U40.5, U40.13, U45.8
/IORQ+: P8.15, U8.1, U31.10, U38.6
/M1*: U1.27, U38.13, U45.9
/M1+: P36.5, U22.7, U38.12
/MREQ*: P9.9, U1.19, U38.11, U39.9
/MREQ+: P36.3, U38.10, U40.2
/MWRT: P1.68, P4.4
/MWRTb: U21.8, U39.13
/NDEF3: P1.66, P6.3
/NMI*: K1.2, RR6.4, U1.17
/NMI*s100: K1.3, P1.12
/PHI: P1.24, R41.2, U21.14
/PU1K-D: P1.72, RR5.5, U28.4
/PU1K-E: P1.3, RR5.6, U28.5
/PU1K-F: RR5.7, U21.1, U37.12
/PU1K-J: RR6.2, U33.12, U33.13, U36.12
/PU1K-JJ: P1.60, RR5.2
/PU1K-K: P1.26, RR6.3, U37.10
/PU1K-N: K2.1, RR6.5
/PU1K-T: P1.18, RR6.8, U25.3, U37.6
/PU1K-Y: P1.58, RR6.9
/PU1K-cp1: P8.17, RR7.8, U27.6
/PU1K-cp2: P8.16, RR7.9, U27.7
/PU1K-waits: K17.3, RR7.10
/PU5K-A: RR7.2, U33.10
/PU5K-B: RR7.3, U34.1, U34.4
/PU5K-C: P8.14, RR7.4, U1.26, U22.11, U34.10
/PU5K-D: RR7.5, U33.1, U33.4
/PWRFAIL*: K1.1, P1.13
/RD*: P9.12, U1.21, U38.9, U39.5, U39.8
/RD+: U21.2, U28.9, U38.8
/REFSH*: U1.28, U40.1, U45.5, U45.6
/RESET*: P1.75, U22.9
/ROM_E-: K18.3, U7.9, U41.14
/ROM_E-33: P9.17, U41.6
/ROM_SELECT: R6.2, U31.13, U36.6
/U4p7: K12.3, P9.8
/U4p9: K11.3, P9.7
/U5p4: K13.3, P9.1
/U5p7: K14.3, P9.2
/U5p9: K16.3, P9.4
/U5p12: K15.3, P9.3
/U6p7: K7.3, P9.6
/U6p9: K6.3, P9.5
/WAIT*: U1.24, U25.12
/WAIT+: R9.2, U25.13, U31.3
/WR*: P9.11, U1.22, U35.13, U38.3, U39.2
/WR+: K8.1, U24.3, U38.4
/Z80_ACTIVE: R2.2, U34.9
/bA0: P9.13, U1.30, U2.9, U27.2, U32.2
/bA1: P9.14, U1.31, U2.8, U27.3, U32.3
/bA2: P8.18, U1.32, U2.7, U14.6, U32.4
/bA3: P8.19, U1.33, U2.6, U14.8, U32.5
/bA4: U1.34, U2.5, U14.11, U32.6
/bA5: P8.20, U1.35, U2.4, U14.13, U32.7
/bA6: P9.15, U1.36, U2.3, U14.15, U32.8
/bA7: P9.16, U1.37, U2.2, U14.17, U32.9
/bA8: U1.38, U8.14, U41.2
/bA9: U1.39, U8.11, U41.3
/bA10: U1.40, U8.5, U41.4
/bA11: U1.1, U8.2, U41.5
/bA12: K12.1, P8.10, U1.2, U7.1
/bA13: K11.1, P8.11, U1.3, U7.2
/bA14: K7.1, P8.12, U1.4, U7.4
/bA15: K6.1, P8.13, U1.5, U7.5
/bA16: K15.2, U12.9
/bA17: K16.2, U12.8
/bA18: K14.2, U12.7
/bA19: K13.2, U12.6
/bINT*: U1.16, U21.11
/pDBIN: P1.78, R35.1
/pSTVAL*: P1.25, R37.1
/pSYNC: P1.76, R36.1
/pSYNCb: K5.2, U21.3, U31.4, U31.9, U31.12
/pWR*: P1.77, R38.1
/pWR*b: U21.5, U24.4, U39.12
/sHLTA: P1.48, U22.18
/sINP: P1.46, U22.16
/sINTA: P1.96, P36.1, U22.12
/sINTAb: U22.8, U45.10
/sM1: P1.44, U22.13
/sMEMR: P1.47, U22.15
/sMEMRb: U22.5, U39.10, U40.10
/sOUT: P1.45, U22.17
/sOUTb: U22.3, U28.12, U39.1, U39.11
/sWO*: P1.97, U22.14
/sWO*b: U22.6, U35.11
GND: C1.2, C2.2, C3.2, C4.2, C8.2, C9.2, C10.2, C11.2, C12.2, C13.2, C14.2, C15.2, C17.2, C18.2, C19.2, C20.2, C21.2, C23.2, C25.2, C26.2, C27.2, C28.2, C30.2, C36.2, C37.2, C38.2, C39.2, C40.2, C41.2, C46.2, C47.2, C49.2, C50.2, C51.2, C52.2, C54.2, C59.2, C60.2, C62.2, D8.2, K4.1, K13.1, K14.1, K15.1, K16.1, K18.1, P1.50, P1.100, P2.2, P2.4, P2.6, P2.8, P3.4, P3.7, P5.4, P5.7, P8.9, P9.18, P34.1, P35.1, Q1.1, Q2.1, Q3.1, SW1.1, SW1.2, SW1.3, SW1.4, SW1.5, SW1.6, SW1.7, SW1.8, SW2.1, SW2.2, SW2.3, SW2.4, SW2.5, SW2.6, SW2.7, SW2.8, SW3.1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
unnamed: U22.19, U25.4
unnamed: U19.1, U19.19, U28.3
unnamed: R36.2, U21.17
unnamed: U21.19, U34.8
unnamed: U40.3, U40.4, U40.12
unnamed: P4.3, U21.12
unnamed: P4.1, U21.13
unnamed: R38.2, U21.15
unnamed: K12.2, U3.5
unnamed: K7.2, U3.3
unnamed: K11.2, U3.4
unnamed: U3.6, U8.4
unnamed: U3.7, U8.7
unnamed: U3.8, U8.9
unnamed: U3.9, U8.12
unnamed: D2.2, Q3.3
unnamed: D2.1, R3.1
unnamed: Q3.2, R6.1
unnamed: RR3.4, SW3.11, U10.13
unnamed: RR3.3, SW3.10, U10.12
unnamed: RR3.2, SW3.9, U10.11
unnamed: U10.1, U31.8
unnamed: U11.1, U31.11
unnamed: RR3.5, SW3.12, U10.14
unnamed: RR3.6, SW3.13, U10.3
unnamed: RR3.7, SW3.14, U10.4
unnamed: RR3.9, SW3.16, U10.6
unnamed: RR3.8, SW3.15, U10.5
unnamed: P6.2, P6.4, U18.2
unnamed: P7.7, U18.11
unnamed: P7.5, U18.12
unnamed: P7.3, U18.13
unnamed: P7.1, U18.14
unnamed: RR2.4, SW2.11, U9.13
unnamed: RR2.3, SW2.10, U9.12
unnamed: RR2.2, SW2.9, U9.11
unnamed: RR2.9, SW2.16, U9.6
unnamed: RR2.8, SW2.15, U9.5
unnamed: RR2.7, SW2.14, U9.4
unnamed: RR2.6, SW2.13, U9.3
unnamed: RR2.5, SW2.12, U9.14
unnamed: RR4.2, SW4.9, U11.11
unnamed: RR4.5, SW4.12, U11.14
unnamed: RR4.4, SW4.11, U11.13
unnamed: RR4.3, SW4.10, U11.12
unnamed: RR4.9, SW4.16, U11.6
unnamed: RR4.8, SW4.15, U11.5
unnamed: RR4.7, SW4.14, U11.4
unnamed: RR4.6, SW4.13, U11.3
unnamed: K8.2, U28.1
unnamed: U33.5, U37.9
unnamed: U7.8, U35.1
unnamed: U7.6, U7.13
unnamed: U7.3, U7.12
unnamed: U7.11, U35.2
unnamed: U35.3, U36.1
unnamed: K4.2, U7.10
unnamed: D1.2, Q2.3
unnamed: D1.1, R1.1
unnamed: Q2.2, R2.1
unnamed: P3.8, P3.11, P6.1
unnamed: U9.7, U35.10
unnamed: U13.1, U32.11
unnamed: U13.2, U32.12
unnamed: U13.3, U32.13
unnamed: U13.4, U32.14
unnamed: U13.5, U32.15
unnamed: U13.6, U32.16
unnamed: U13.7, U32.17
unnamed: U13.8, U32.18
unnamed: U24.5, U28.6
unnamed: U24.6, U31.2
unnamed: R16.2, U13.20, U41.12
unnamed: U13.23, U41.18
unnamed: U13.22, U41.17
unnamed: U13.19, U41.16
unnamed: U13.21, U41.15
unnamed: K18.2, U41.9
unnamed: U13.13, U30.5
unnamed: U13.9, U30.2
unnamed: U13.10, U30.3
unnamed: U13.11, U30.4
unnamed: D8.1, R4.1
unnamed: U13.14, U30.6
unnamed: U13.15, U30.7
unnamed: U13.16, U30.8
unnamed: U13.17, U30.9
unnamed: K17.2, U31.1
unnamed: K17.1, U24.12
unnamed: R11.2, U13.18, U30.1, U30.19, U41.11
unnamed: K4.3, R7.2
unnamed: U35.12, U45.4
unnamed: D3.1, R8.1
unnamed: D3.2, Q1.3
unnamed: Q1.2, R9.1
unnamed: K10.2, U15.2
unnamed: K5.1, U15.7
unnamed: RR1.4, SW1.11, U15.13
unnamed: RR1.3, SW1.10, U15.12
unnamed: RR1.2, SW1.9, U15.11
unnamed: U15.1, U36.8
unnamed: RR1.9, SW1.16, U15.6
unnamed: RR1.8, SW1.15, U15.5
unnamed: RR1.7, SW1.14, U15.4
unnamed: RR1.6, SW1.13, U15.3
unnamed: RR1.5, SW1.12, U15.14
unnamed: K3.1, U36.9, U40.11
unnamed: K3.2, U29.12
unnamed: K5.3, K9.2
unnamed: K9.3, U29.8
unnamed: K9.1, U29.9
unnamed: K3.3, U21.4, U36.10
unnamed: U22.4, U39.4
unnamed: K6.2, U3.2
unnamed: U22.2, U38.2
unnamed: U36.11, U40.6
unnamed: U36.2, U40.9
unnamed: R37.2, U21.16
unnamed: R35.2, U21.18
unnamed: U33.2, U45.1
unnamed: K2.2, U34.12, U34.13
unnamed: U33.8, U45.3
unnamed: U27.1, U28.11
unnamed: P2.1, U14.12
unnamed: P2.3, U14.14
unnamed: P2.5, U14.16
unnamed: P2.7, U14.18
unnamed: U14.19, U25.1
unnamed: U25.2, U28.13
unnamed: U10.7, U35.5
unnamed: U24.13, U35.8
unnamed: U35.6, U35.9
unnamed: U11.7, U35.4
unnamed: P36.2, P36.4, P36.6, U31.5
unnamed: U9.1, U31.6
unnamed: K10.1, U21.6, U29.11, U33.3, U34.3, U34.11, U36.4
unnamed: U33.9, U37.1, U37.3, U37.5
unnamed: K2.3, U33.6
VCC: C2.1, C3.1, C4.1, C8.1, C9.1, C10.1, C11.1, C12.1, C13.1, C14.1, C15.1, C17.1, C18.1, C19.1, C20.1, C21.1, C23.1, C25.1, C26.1, C27.1, C28.1, C30.1, C36.1, C37.1, C38.1, C39.1, C40.1, C41.1, C46.1, C47.1, C49.1, C50.1, C51.1, C52.1, C54.1, C59.1, C60.1, C62.1, P3.1, P3.14, P5.1, P5.14, P9.19, P9.20, R1.2, R3.2, R4.2, R5.1, R7.1, R8.2, R11.1, R16.1, R41.1, RR1.1, RR2.1, RR3.1, RR4.1, RR5.1, RR6.1, RR7.1, U1.11, U2.20, U3.20, U7.14, U8.16, U9.10, U9.16, U10.10, U10.16, U11.10, U11.16, U12.20, U13.24, U14.20, U15.10, U15.16, U18.1, U18.7, U18.9, U18.10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

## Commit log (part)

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2013-07-22 Z80-FPGA-SBC: REV 1.0 layout and fab gerbers (XC9572XL CPLD2 + MAX3002 translators)
    Source: Z80 Board ANTS_MOD 2/ECB SBC V2/gerbers/ (plotted 2013-07-22 15:39) and
    ECB SBC V2/SBC.000, committed as rev1.0/SBC_rev1.0.brd.
    SBC.000 is the last save of the REV 1.0 board by PCBNEW 2011-07-08 (header
    '7/22/2013 3:35:24 PM'), kept by KiCad as a backup copy when the board was later
    re-saved by a newer KiCad. It is the only surviving REV 1.0 layout: its vias +
    through-hole pads (1249 + 457 = 1706) match the 1706 holes in gerbers/SBC.drl.
2013-08-02 Backplane-18-Slot rev1: PCB layout
    Source: S100 Backplane ANTS_MOD/S100 Backplane-001/BACKUPS/backup 03082013 0543/S100 Backplane-001
2013-08-04 Backplane-18-Slot rev1: add second logo; layout
    Source: S100 Backplane ANTS_MOD/S100 Backplane-001/BACKUPS/backup 05082013 0041/S100 Backplane-001
2013-08-25 Z80-FPGA-SBC: REV 2 rework: drop CPLD2/MAX3002s, 74LS245/541 S-100 buffers, new regulators
    Source: Z80 Board ANTS_MOD 2/backyp 26082013 1143/ECB SBC V2 (folder name typo 'backyp' is original).
    Schematic started from the N8VEM SBC V2 (Andrew Lynch / N8VEM); see README credits.
    Layout text still reads 'REV 1.0' at this point.
2013-08-26 Z80-FPGA-SBC: regenerate netlist
    Source: Z80 Board ANTS_MOD 2/ECB SBC V2 (working folder): SBC.net.
2013-09-09 Z80-FPGA-SBC: REV 2.0 layout
    Source: Z80 Board ANTS_MOD 2/ECB SBC V2 (working folder): SBC.brd.
2013-10-07 Backplane-18-Slot rev1: 18 slots; PIC18F2550 PSU control; XC6SLX9/FT232R experiments; first gerbers
    Source: S100 Backplane ANTS_MOD/S100 Backplane-001/BACKUPS/backup 07102013 1647/S100 Backplane-001
2013-10-07 Backplane-18-Slot rev1: layout
    Source: S100 Backplane ANTS_MOD/S100 Backplane-001/BACKUPS/backup 08102013 0115/S100 Backplane-001
2013-10-18 Backplane-18-Slot rev1: layout
    Source: S100 Backplane ANTS_MOD/S100 Backplane-001/BACKUPS/backup 19102013 0001/S100 Backplane-001
2013-10-19 Backplane-18-Slot rev1: layout
    Source: S100 Backplane ANTS_MOD/S100 Backplane-001/BACKUPS/backup 19102013 1038/S100 Backplane-001
2013-10-19 Backplane-18-Slot rev1: layout and project settings
    Source: S100 Backplane ANTS_MOD/S100 Backplane-001/BACKUPS/backup 20102013 1136/S100 Backplane-001
2013-11-02 S6LX9-FPGA-IO: schematic tweaks (R1 4K8 to 6K8), placement
    Source: S100 FPGA_TIMER_INT_CONTROLLER/backups/03112013 0658 (KiCad project TMRINT, original folder name FPGA_TIMER_INT_CONTROLLER)
2014-03-11 Backplane-18-Slot rev1: Rev 1.0 final: ATX PSU split off, 15.7x8.0 in board, gerbers and BOM
    Source: S100 Backplane ANTS_MOD/S100 Backplane-001/S100 Backplane-001
    S100-Backplane.pro is taken from S100 Backplane ANTS_MOD/V1 - backup 22-10-2015 (same content, saved 2013-10-20); the working-folder copy was only re-saved in 2016.
2014-03-20 SRAM-8MB rev1: first schematic and layout
    Source: S100 8MB SRAM proto1/BACKUPS/20032014 1803
2014-03-20 SRAM-8MB rev1: routed board
    Source: S100 8MB SRAM proto1/BACKUPS/20032014 2037
2014-04-04 NOR-SRAM-Loader cpld: U11 schematic v2
    Source: Xilinx Projects/8Mb NOR to SRAM Board U11/U11v2.sch
2014-04-14 Flash-UART: KiCad schematic and placed PCB (16550, FT232R, CH341A, 4x M25P80, XC95288XL)
    Source: S100_B1FLASHUART/backups/14042014 2051
    PCB placed, not yet routed.
2014-04-18 Flash-UART: routed PCB and gerbers; add CPLD I/O headers P2/P10
    Source: S100_B1FLASHUART/backups/05052014 FINAL after printed
    Gerbers dated 2014-04-16; one GND label added to the schematic on 2014-04-18.
    The working folder S100_B1FLASHUART/ is identical apart from a KiCad autosave.
2014-05-08 Flash-UART cpld: first U20 test schematic and pin map (LEDs D2/D3)
    Source: Xilinx Projects/S100_BFU1_Rev1/outdated (the first U20v1.sch and pinmap.ucf, later kept as cpld/outdated/)
2014-06-04 Flash-UART cpld: ISE project, reset logic, port EEh TMA0-3 register
    Source: Xilinx Projects/S100_BFU1_Rev1/backups/04-06-2014 1656
2014-06-04 Flash-UART cpld: SPI bit-bang ports 90h-94h (CLK, Din, CS, Dout, DONE LED)
    Source: Xilinx Projects/S100_BFU1_Rev1/backups/04-06-2014 2258 working
    The later backup "16-17-2015 changing flash cs to use smaller flash" has identical design files.
2014-06-06 Z80-CPU v2: board layout (unrouted)
    Source: S100 Z80 version2/backups/06-06-2014 2143
2014-06-23 S6LX9-FPGA-IO: U30v1 gateware schematic, OUT F0h latch to six LEDs
    Source: Xilinx Projects/TIMER_INT Board/U30v1.sch (Xilinx ISE schematic)
2014-07-16 Z80-CPU v3: schematic and placement rework
    Source: S100 Z80 version3/backups/17-07-2014 0138
2014-07-17 Z80-CPU v3: routed REV 2.0 board and gerbers
    Source: S100 Z80 version3/backups/20-07-2014
    Newest file is 2014-07-18 00:18 (the gerber time); the folder name says 20-07.
2014-07-20 Z80-CPU v3: schematic changes after the gerbers (unrouted board)
    Source: S100 Z80 version3/backups/20-07-2014 1447
2014-07-22 Z80-CPU v3: board layout (unrouted)
    Source: S100 Z80 version3/backups/23-07-2014 0840
2014-08-02 Bus-Terminator: schematic and first parts placement
    Source: S100 Bus Terminator v1/backups/03-08-2014 1155
    Schematic of the active terminator card; board has parts placed, no tracks yet.
2014-08-03 Bus-Terminator: PRESET/EXTCLR jumpers JP6/JP7, routed board, gerbers
    Source: S100 Bus Terminator v1 (working folder) and S100 Bus Terminator v1/GERBERS
    Adds JP6/JP7, mounting holes, copper/silk text; 2-layer routing with GND pours; fab gerbers and drill file.
2015-04-19 Z80-CPU v2: Logisim sketch of address/IORQ decode logic
    Source: S100 Z80 version2/Logisim circuits/1.circ (Logisim 2.7.1; labels A14, A15, IOREQ, S0, S1).
2015-04-25 x86-Memory-Adapter: adapter LT3081 adjustable rail and 3.3V/5V source jumpers; first routing
    Source: S100 4GB DRAM BOARD/S100 80386 SRAM DB Version 1/backups/25-04-2015 1211
2015-04-29 x86-Memory-Adapter: 4Mbit SRAM module, 4x 128Kx8 SRAM + XC9536XL; parts placed
    Source: S100 4GB DRAM BOARD/4Mem board v1/backups/29-04-2015 1556
    Board unrouted.
2015-05-03 DRAM-4GB-Unfinished: start 4Mem v2 from the 4Mbit module outline; place XC6SLX45 FGG484 and DDR3 DIMM socket
    Source: S100 4GB DRAM BOARD/4Mem board v2/backups/03-05-2015 1356
2015-05-03 DRAM-4GB-Unfinished: PCB tweaks
    Source: S100 4GB DRAM BOARD/4Mem board v2/backups/04-04-2015 0917 (folder name says 04-04-2015 but its files are dated 2015-05-04 08:52 NZ; the name should be 04-05-2015)
2015-05-17 DRAM-4GB-Unfinished: connect all P8/P9 signals to the FPGA; BGA power fanout
    Source: S100 4GB DRAM BOARD/4Mem board v2/backups/23-05-2015 2046 (newest file is 2015-05-17)
2015-06-21 DRAM-4GB-Unfinished: add PIC18F2520, XCF08P config flash and 2.5 V clock; last PCB edits; DigiKey parts list
    Source: S100 4GB DRAM BOARD/4Mem board v2/(top level) (working folder; .dsn/.ses/.bak, BMP screenshots, datasheets and saved web pages left out)
2015-06-27 Z80-CPU v4: new revision with XC9572 CPLD (IC1), from v3
    Source: S100 Z80 version4/backups/28-06-2015 0854 (the same folder also exists, byte-identical, in S100 Z80 version5/backups)
2015-06-28 Z80-CPU v4: routed trial
    Source: S100 Z80 version4/backups/29-06-2015 morning (the same folder also exists, byte-identical, in S100 Z80 version5/backups)
    Newest file is 2015-06-28 18:59.
2015-06-29 Z80-CPU v4: schematic, netlist and placement
    Source: S100 Z80 version4/backups/30-06-2015 1801 (the same folder also exists, byte-identical, in S100 Z80 version5/backups)
2015-07-04 Z80-CPU cpld: IC1v1 schematic, PISO block, V4 pin map and JEDEC
    Source: Xilinx Projects/Z80_Board_V4 (ISE 14.7, xc9572-10 PC84). PISO.sch (test1.sch) is the PISO shift-register sub-sheet.
2015-07-12 x86-Memory-Adapter: SRAM module trial DDR3 DIMM footprint removed
    Source: S100 4GB DRAM BOARD/4Mem board v1 ('4Mem board v1.kicad_pcb' of 2015-07-12, '4Mem board v1.pro')
    Routing unchanged; only the DIMM footprint was deleted.
2015-07-22 Flash-UART cpld: port 95h selects flash U16 (smaller 25L020) or U14; PIC line joins reset
    Source: Xilinx Projects/S100_BFU1_Rev1/backups/10-08-2015 1907 (overlay: this backup has no outdated/ folder)
    Change started in "16-17-2015 changing flash cs to use smaller flash" (16 Jul 2015).
2015-07-25 XC9500-IO: schematic and placement edits
    Source: S100 XC9500 Ver1/backups/25-07-2015 2032
2015-07-26 XC9500-IO: placement tweaks before autorouting
    Source: S100 XC9500 Ver1/backups/27-06-2015 1904 before ses 2. The folder name says 27-06 but the files are dated 27-07-2015. Only the board file differs from the previous snapshot.
2015-07-28 Z80-CPU v4: routed REV 4.0 board and gerbers sent to PCBway
    Source: S100 Z80 version4/GERBERS (an identical copy is in GERBERS/SENT to PCBway 28-07-2015) and S100 Z80 version4/s100_Z80 V4.kicad_pcb-bak.
    The routed board at gerber time (2015-07-28 09:27) survives as s100_Z80 V4.kicad_pcb-bak; it is committed as s100_Z80 V4.kicad_pcb.
    The .drl was re-exported from gerbv as RS-274X at 14:41.
2015-08-01 S6LX9-FPGA-IO: U30v2 gateware (bus buffer enable qualified by pWR*), ISE 14.7 project
    Source: Xilinx Projects/TIMER_INT Board/U30v2.sch and Xilinx Projects/TIMER_INT Board/TIMER_INT1/TIMER_INT1.xise
2015-08-06 Z80-CPU cpld: ISE project file for IC1v1
    Source: Xilinx Projects/Z80_Board_V4/Z80_Board_V4/Z80_Board_V4.xise
2015-08-08 Z80-CPU cpld: IC1v2 schematic
    Source: Xilinx Projects/z80v42/IC1v2.sch
2015-08-10 Z80-CPU v2: schematic notes and rework wiring (WR+/RD+)
    Source: S100 Z80 version2/s100_Z80 V2.sch and -cache.lib (working folder).
2015-08-13 XC9500-IO: schematic rev after the gerbers - U11 74LS682 for A5-A7, 12-way SW1, VI0* on the vector jumper
    Source: S100 XC9500 Ver1 working folder (schematic and cache lib 13-08-2015, netlist and cmp 01-08-2015).
2015-12-13 Backplane-18-Slot rev2: Rev 2 schematic (Q13/R46 removed, U23 74LS05) and first gerbers
    Source: S100 Backplane ANTS_MOD/V2 - S100 Backplane v002/ (S100-Backplanev2.bak saved 2015-10-27 is committed as S100-Backplanev2.sch; .net/.cmp 2015-10-27; Gerbers/old 1 dated 2015-12-14). No board 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
2015-12-20 Z80-CPU v5: new revision from v4 (2764 ROM, 74LVC573 latches)
    Source: S100 Z80 version5/backups/20-12-2015
2015-12-25 SRAM-8MB cpld: board select, 8/16-bit strobes and even/odd bank decode; JED
    Source: Xilinx Projects/8MB SRAM BOARD REV2/ (U4v1.sch, pinmap.ucf) and Xilinx Projects/8MB SRAM BOARD REV2/SRAM_B_V2/ (SRAM_B_V2.xise, U4v1.jed)
2015-12-28 Flash-UART cpld: U20v2 with port 96h flash select and idle-high TMA outputs
    Source: Xilinx Projects/S100_BFU1_Rev1 (working folder)
2015-12-28 Z80-CPU cpld: IC1v2_7, pin map, ISE project and JEDEC
    Source: Xilinx Projects/z80v42 (ISE 14.7, xc9572-7 PC84; top IC1v2_7). The pin map header says 'PIN MAP OF IC1 on Z80 Board V4'.
2016-01-05 PIC-SPI: start from the Flash-UART layout; new schematic with 8259A, DS1305, 2x MCP23S08, 8x M25P80
    Source: S100 PIC_SPI_v1/backups/05-01-2016 1412
    The .net and .cmp in this snapshot are unchanged copies carried over from the Flash-UART (S100_B1FU) board, dated 2014-04-16; the .kicad_pcb is the Flash-UART layout with its tracks removed.
2016-01-09 PIC-SPI: rip up tracks for a reroute
    Source: S100 PIC_SPI_v1/backups/09-01-2016 1434 reroute
2016-01-09 PIC-SPI: autorouted layout (5100 tracks, 449 vias), manual track tweaks
    Source: S100 PIC_SPI_v1 (working folder)
2016-01-11 x86-Memory-Adapter: SRAM module spare SRAM_512KB symbol (off-sheet)
    Source: S100 4GB DRAM BOARD/4Mem board v1 (working folder)
    The SRAM_512KB symbol is unannotated, placed outside the sheet and is not in the netlist.
2016-01-12 x86-Memory-Adapter: adapter general I/O and SPI SRAM removed; board re-routed
    Source: S100 4GB DRAM BOARD/S100 80386 SRAM DB Version 1 (working folder)
    No gerbers were made from this final layout; GERBERS/ is the April 2015 plot.
